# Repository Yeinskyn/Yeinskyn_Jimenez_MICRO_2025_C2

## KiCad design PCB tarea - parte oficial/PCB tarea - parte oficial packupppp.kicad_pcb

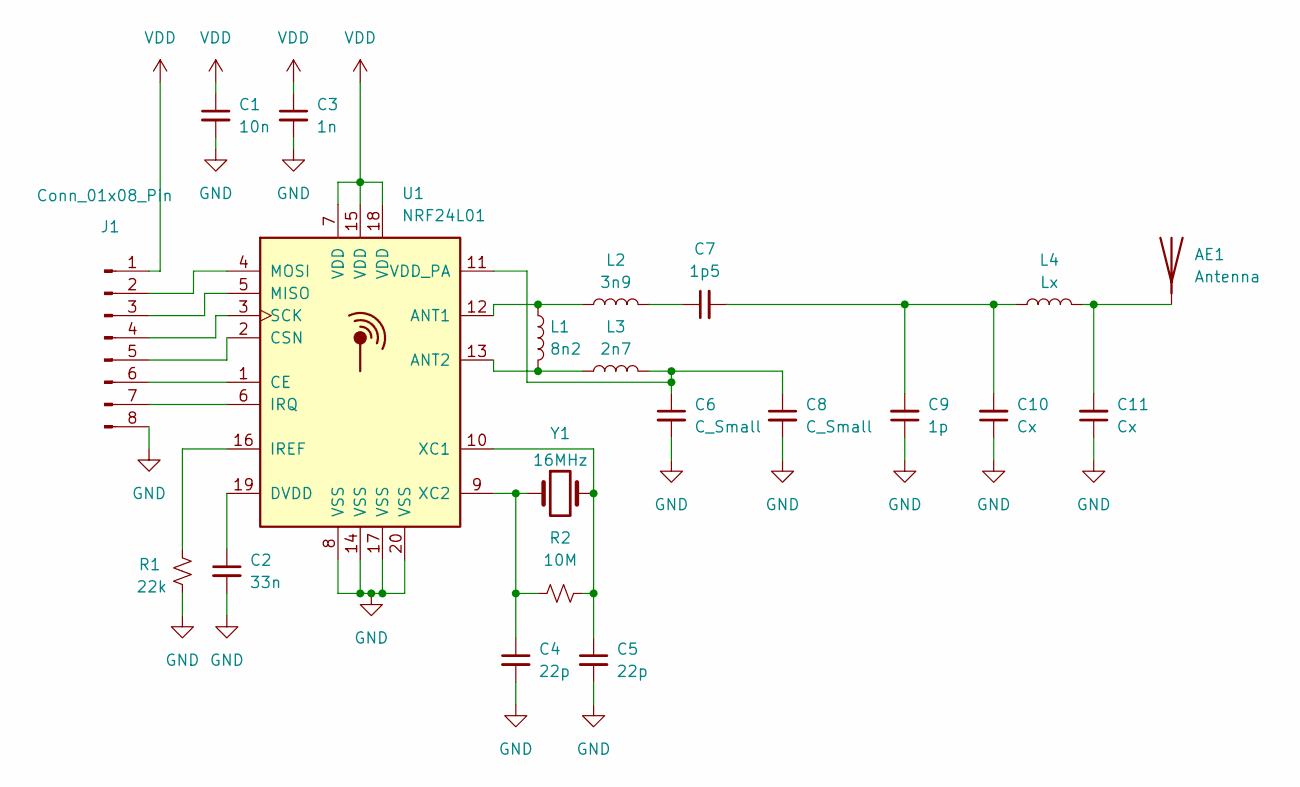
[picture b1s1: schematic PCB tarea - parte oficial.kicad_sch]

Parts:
AE1: Antenna; Texas_SWRA117D_2.4GHz_Right
C1: 10n; C_0402_1005Metric
C2: 33n; C_0402_1005Metric
C3: 1n; C_0402_1005Metric
C4, C5: 22p; C_0402_1005Metric
C6, C8: C_Small; C_0402_1005Metric
C7: 1p5; C_0402_1005Metric
C9: 1p; C_0402_1005Metric
C10, C11: Cx; C_0402_1005Metric
J1: Conn_01x08_Pin; Hirose_DF13-08P-1.25DSA_1x08_P1.25mm_Vertical
L1: 8n2; L_0402_1005Metric
L2: 3n9; L_0402_1005Metric
L3: 2n7; L_0402_1005Metric
L4: Lx; L_0402_1005Metric
R1: 22k; R_0402_1005Metric
R2: 10M; R_0402_1005Metric
U1: NRF24L01; QFN-20-1EP_4x4mm_P0.5mm_EP2.5x2.5mm
Y1: 16MHz; Crystal_SMD_3215-2Pin_3.2x1.5mm

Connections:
GND: C1.2, C2.2, C3.2, C4.2, C5.2, C6.2, C8.2, C9.1, C10.1, C11.1, J1.8, R1.2, U1.8 (VSS), U1.14 (VSS), U1.17 (VSS), U1.20 (VSS)
unnamed: AE1.1 (A), C11.2, L4.2
unnamed: C7.1, L2.2
unnamed: C7.2, C9.2, C10.2, L4.1
unnamed: J1.2, U1.4 (MOSI)
unnamed: J1.3, U1.5 (MISO)
unnamed: J1.4, U1.3 (SCK)
unnamed: J1.5, U1.2 (CSN)
unnamed: J1.6, U1.1 (CE)
unnamed: J1.7, U1.6 (IRQ)
unnamed: L1.1, L2.1, U1.12 (ANT1)
unnamed: L1.2, L3.1, U1.13 (ANT2)
unnamed: C2.1, U1.19 (DVDD)
unnamed: R1.1, U1.16 (IREF)
unnamed: C6.1, C8.1, L3.2, U1.11 (VDD_PA)
unnamed: C5.1, R2.2, U1.10 (XC1), Y1.2
unnamed: C4.1, R2.1, U1.9 (XC2), Y1.1
VDD: C1.1, C3.1, J1.1, U1.7 (VDD), U1.15 (VDD), U1.18 (VDD)

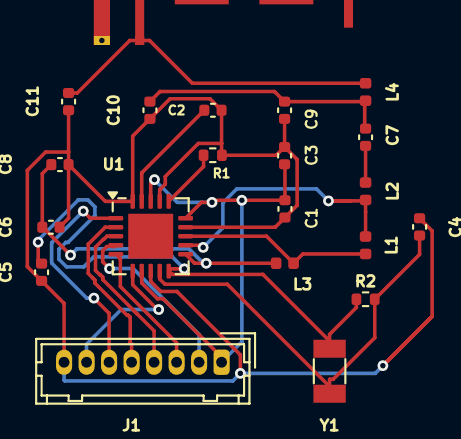
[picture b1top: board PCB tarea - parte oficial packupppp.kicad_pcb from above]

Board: 2 copper layers, 21 parts (0 on the bottom side), 18 nets.

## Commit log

2025-06-27 Eliminando archivos innecesarios del repositorio
2025-07-17 Eliminé archivo innecesario
2025-07-17 Borrado documento innecesario
